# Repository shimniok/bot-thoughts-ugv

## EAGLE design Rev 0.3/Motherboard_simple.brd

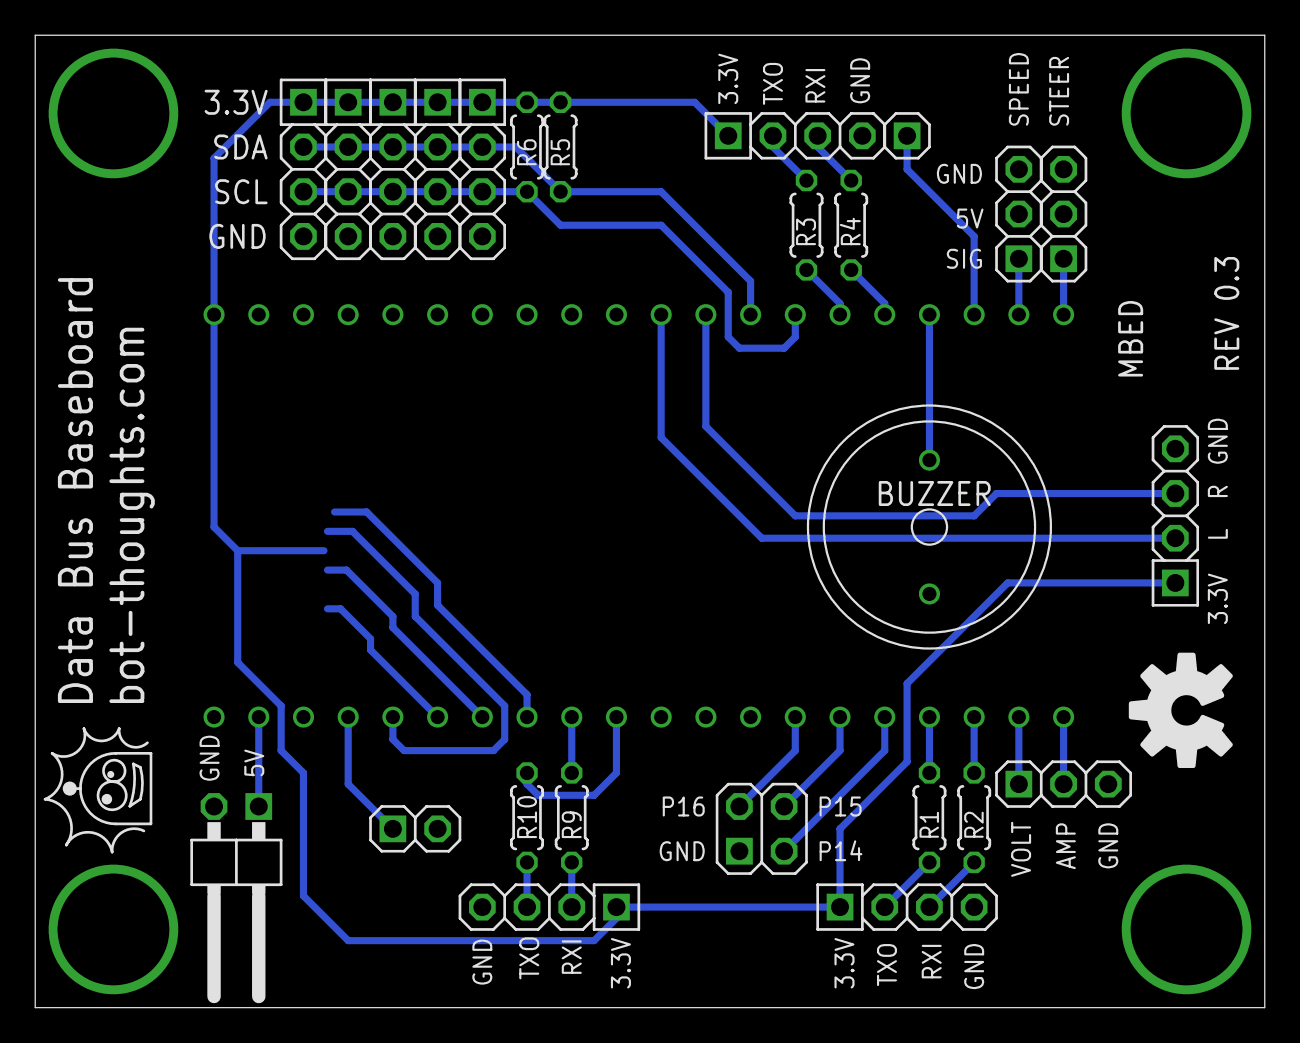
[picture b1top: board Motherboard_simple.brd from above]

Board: 2 copper layers, 69.8 x 55.2 mm, 27 parts (1 on the bottom side), 33 nets.

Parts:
BUZZER: 1438-TWT-R; BUZZER_14MM_PTH
JP1: BUTTONS; 2X02
JP2: UART1; 1X04-S
JP3: POWER; 1X02/90-S
JP4: RST; 1X02-S
JP5, JP11, JP12, JP13, JP14: I2C; 1X04-S
JP6: UART3; 1X04-S
JP7: PPS; 1X01-S
JP8: SPEED; 1X03-S
JP9: STEER; 1X03-S
JP10: UART2; 1X04-S
JP15: ENCODERS; 1X04-S
JP17: VA; 1X03-S
MBED: MBED_NXP_LPC1768; MBED-KIT
R1, R2, R3, R4, R9, R10: 220; 0204/5
R5, R6: 2.2K; 0204/5
U2: USD-SOCKETNEW; MICRO-SD-SOCKET-PP

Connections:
!CS1: MBED.P$8, U2.2
!RESET: JP4.1, MBED.NR
+3V3: JP2.1, JP5.1, JP6.1, JP10.1, JP11.1, JP12.1, JP13.1, JP14.1, JP15.1, MBED.VOUT, R5.2, R6.2, U2.4
+5V: JP3.1, MBED.VIN
AMP: JP17.2, MBED.P$20
ENC_LEFT: JP15.2, MBED.P$30
ENC_RIGHT: JP15.3, MBED.P$29
GND: BUZZER.P$2, JP1.1, JP2.4, JP3.2, JP4.2, JP5.4, JP6.4, JP8.3, JP9.3, JP10.4, JP11.4, JP12.4, JP13.4, JP14.4, JP15.4, JP17.3, MBED.GND, U2.6, U2.GND1, U2.GND3
MISO1: MBED.P$6, U2.7
MOSI1: MBED.P$5, U2.3
unnamed: JP6.2, R1.2
unnamed: JP6.3, R2.2
unnamed: JP1.2, MBED.P$14
unnamed: JP17.1, MBED.P$19
unnamed: JP1.4, MBED.P$15
unnamed: JP1.3, MBED.P$16
unnamed: JP2.2, R3.2
unnamed: JP2.3, R4.2
unnamed: BUZZER.P$1, MBED.P$24
unnamed: JP10.2, R9.2
unnamed: JP10.3, R10.2
PPS: JP7.1, MBED.P$23
RXD1: MBED.P$25, R4.1
RXD2: MBED.P$10, R10.1
RXD3: MBED.P$18, R2.1
SCK1: MBED.P$7, U2.5
SCL: JP5.3, JP11.3, JP12.3, JP13.3, JP14.3, MBED.P$27, R6.1
SDA: JP5.2, JP11.2, JP12.2, JP13.2, JP14.2, MBED.P$28, R5.1
SPEED: JP8.1, MBED.P$22
STEER: JP9.1, MBED.P$21
TXD1: MBED.P$26, R3.1
TXD2: MBED.P$9, R9.1
TXD3: MBED.P$17, R1.1

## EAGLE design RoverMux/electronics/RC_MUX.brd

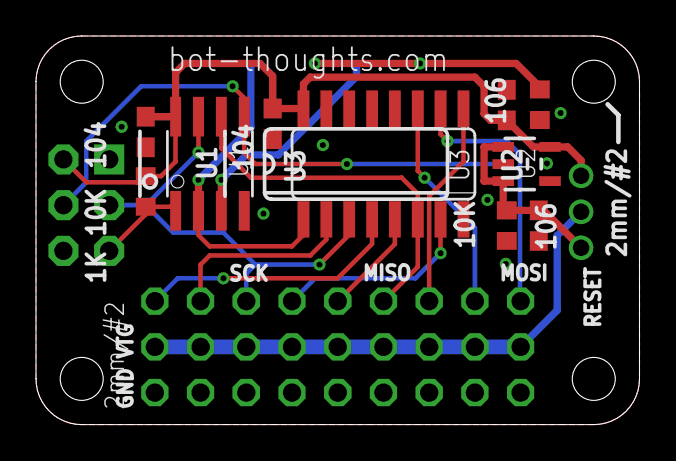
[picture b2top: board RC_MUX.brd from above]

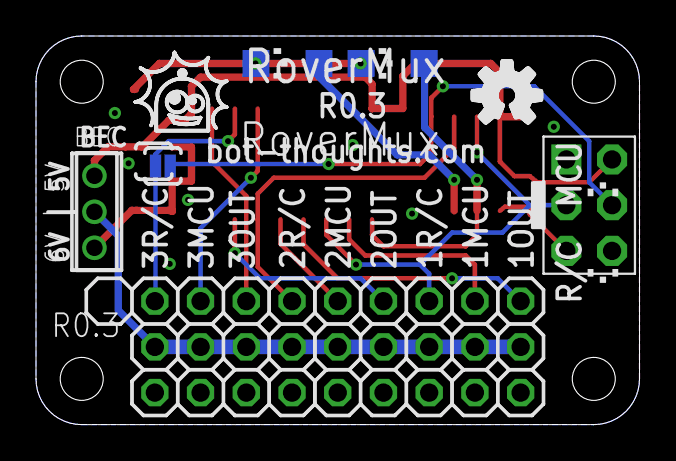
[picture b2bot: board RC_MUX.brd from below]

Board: 2 copper layers, 33.5 x 21.6 mm, 24 parts (14 on the bottom side), 18 nets.

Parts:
C2, C4: 104; C0603
C3, C5: 106; C0603
J1: ISP; CON6P2R
JP1: PWRSEL; 1X03M
JP11: 1MCU; 1X03-S
JP12: 2MCU; 1X03-S
JP13: 3MCU; 1X03-S
JP21: 1R/C; 1X03-S
JP22: 2R/C; 1X03-S
JP23: 3R/C; 1X03-S
JP31: 1OUT; 1X03-S
JP32: 2OUT; 1X03-S
JP33: 3OUT; 1X03-S
LED1: MCU; CHIPLED_1206
LED2: R/C; CHIPLED_1206
R1, R4: 10K; R0603
R2: 1K; R0603
SJ1: CH3; SJ_2S-NOTRACE
U1: TINY13; SO08
U2: MCP1824T; SOT23-5
U3: 74LS157D; SO16

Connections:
!RESET: J1.5, R1.1, U1.1
+5V: C2.1, C4.1, C5.1, J1.2, JP1.1, R1.2, U1.8, U2.5, U3.16
+7V: JP1.2, JP11.2, JP12.2, JP13.2, JP21.2, JP22.2, JP23.2, JP31.2, JP32.2, JP33.2
A: LED1.A, U1.3
B: LED2.A, U1.2, U3.1
CH1MCU: JP11.1, U3.2
CH1OUT: JP31.1, U3.4
CH1RX: J1.3, JP21.1, U1.7, U3.3
CH2MCU: JP12.1, U3.5
CH2OUT: JP32.1, U3.7
CH2RX: JP22.1, U1.6, U3.6
CH3MCU: JP13.1, U3.11
CH3OUT: JP33.1, U3.9
CH3RX: JP23.1, SJ1.2, U3.10
GND: C2.2, C3.2, C4.2, C5.2, J1.6, JP11.3, JP12.3, JP13.3, JP21.3, JP22.3, JP23.3, JP31.3, JP32.3, JP33.3, R2.2, R4.1, U1.4, U2.2, U3.8, U3.13, U3.14, U3.15
MOSI: J1.4, SJ1.1, U1.5
unnamed: LED1.C, LED2.C, R2.1
REGIN: C3.1, JP1.3, R4.2, U2.1, U2.3

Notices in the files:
parts and their libraries:
SparkFun: Licensing: CC v3.0 Share-Alike You are welcome to use this library for commercial purposes.
